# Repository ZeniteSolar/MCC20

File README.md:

# MCC20
**M**ódulo **C**ontrolador de **C**arga 2020  
Embarcação Guarapuvu II  
Equipe Zênite Solar  

### Sobre

Este módulo é responsável por gerenciar o carregamento da bateria e a operação do painel no seu ponto de maxima potencia 

#### Requisitos e Abordagens
1. [Encontrar o ponto de maxima potencia (MPP) do painel solar](#codigo)
    - Utilizar a tecnica perturbar e observar (p&o) para achar o MPP
    - Ao iniciar varrer o duty cicle para iniciar no MPP
    - Se a potencia for 0 fazer o barrido novamente 
2. Medir a Potencia do painel
    - Usar um ina826 para medir a tensao do painel
    - Usar um ina240 para medir a corrente do painel
    
3. Eficiencia energetica
    - Indutores
        - Utilizar fios em paralelo para diminuir o *skin effect*
        - Utilizar indutor acoplado (não implementado)
    - Capacitores
        - Utilizar capacitores SMD com baixa ESR
    - Chaves
        - Utilizar snubber para amortecer oscilações e picos de tensão
        - Utilizar chaves com baixa Rdson e rapidas
        - Utilizar conversor sincrono (não implementado)
    - Frequencia
        - Utilizar frequencia que tenha uma boa relação entre perdas nas chaves e volume do conversor
    - Layout
        - Baixa indutancia no braço (entre chaves)
        - Trilhas curtas
    - Snubber
        - Equilibrio entre sobre-tensão nas chaves e potencia dissipada
4. Robustez
    - Chaves em regime seguro
        - Snubber
        - Layout
    - Proteção *under load* (nao implementado)
    - Capacitores em regime seguro
        - Tensao maxima >Vpan+Vbat
    - Tolerancia termica
        - Projetar assumindo que a temperatura ambiente é 50°
    - Layout simples de montar por metodo artesanal (transferencia termica)

```
testee
```

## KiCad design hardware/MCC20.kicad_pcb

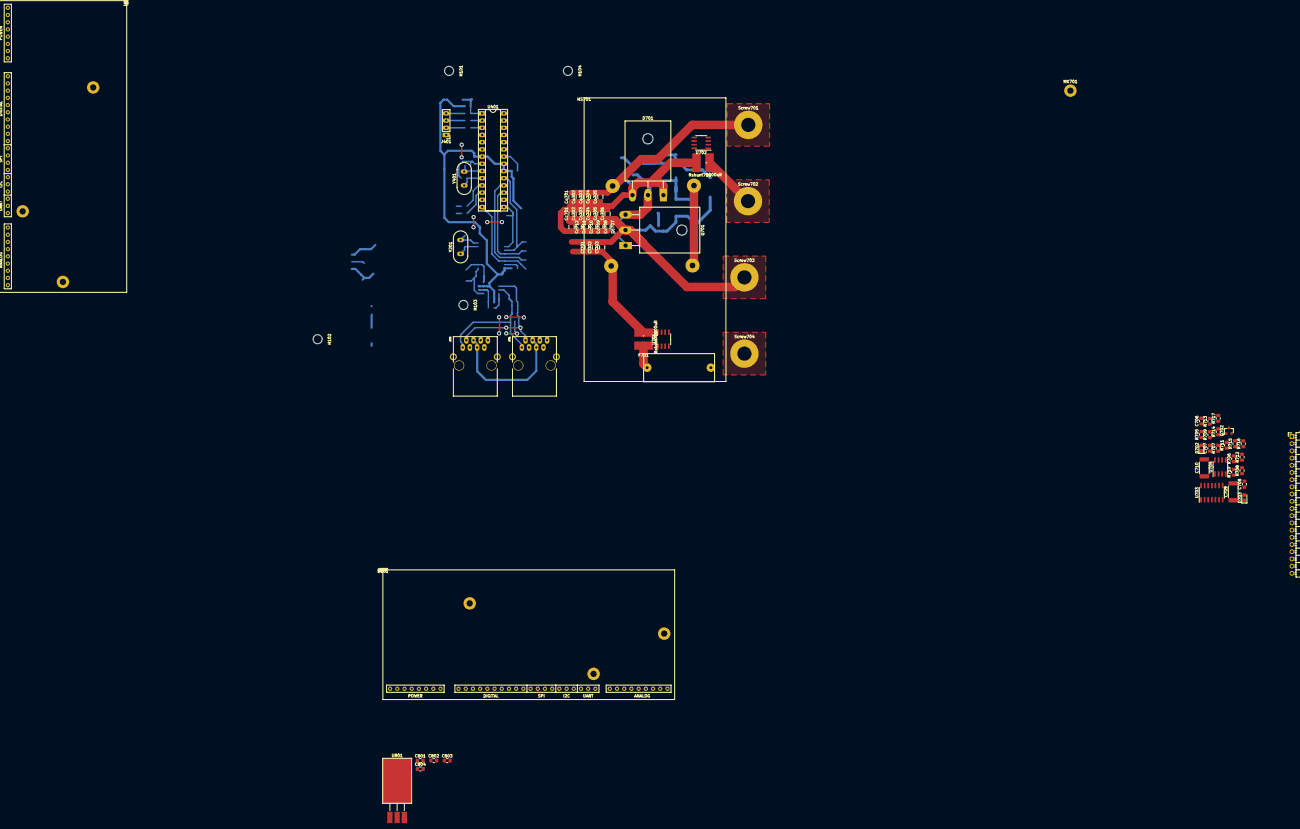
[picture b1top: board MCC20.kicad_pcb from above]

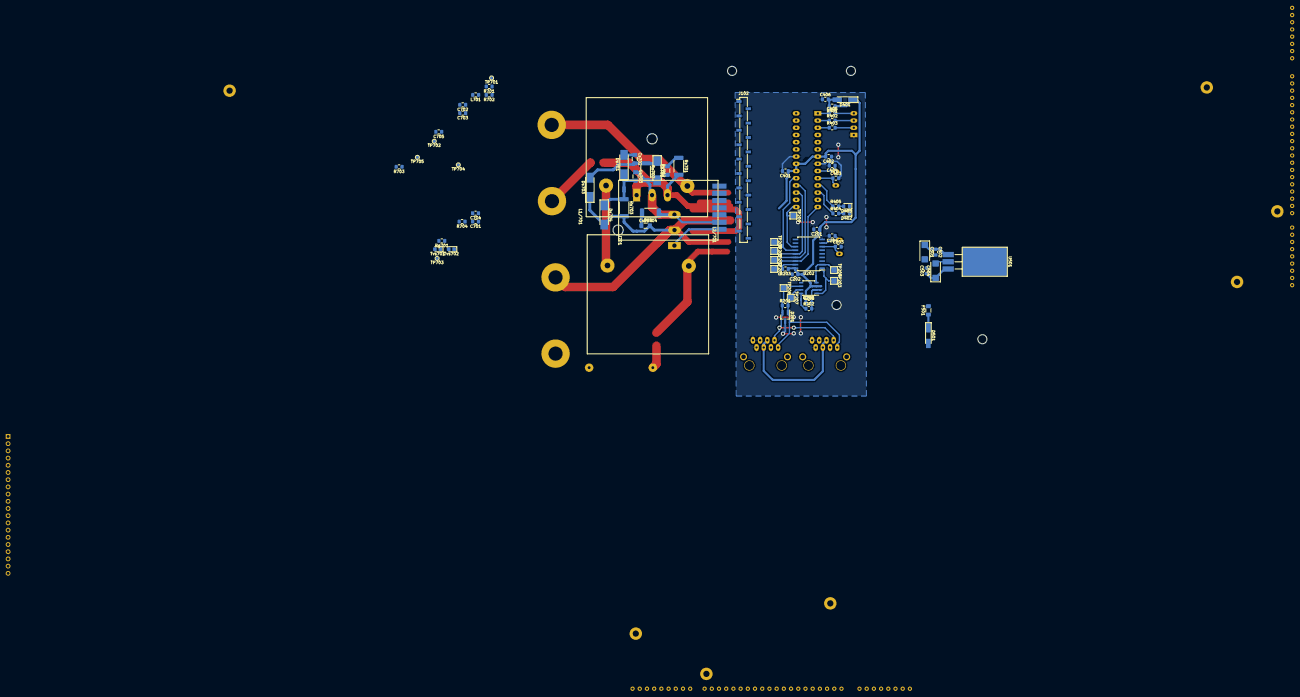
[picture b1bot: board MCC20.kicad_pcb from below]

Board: 2 copper layers, 149 parts (75 on the bottom side), 79 nets.

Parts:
C201, C202, C205, C401, C402, C405, C406, C502, C503, C701, C702, C703, C704, C708, C802, C803: 100nF; C_0805_2012Metric_Pad1.15x1.40mm_HandSolder
C203, C204, C403, C404: 22pF; C_0805_2012Metric_Pad1.15x1.40mm_HandSolder
C501, C504: 1uF; CP_EIA-6032-20_AVX-F_Pad2.25x2.35mm_HandSolder
C705, C801, C804: 10uF; C_0805_2012Metric_Pad1.15x1.40mm_HandSolder
C706: 100n; C_0805_2012Metric_Pad1.15x1.40mm_HandSolder
C707: 1n; C_0805_2012Metric_Pad1.15x1.40mm_HandSolder
C709, C710: 10u; C_2512_6332Metric_Pad1.52x3.35mm_HandSolder
Cc701, Cc702, Cc703, Cc704, Cc705, Cc706, Cc707, Cc708, Cc709, Cc710, Cc711, Cc712: 1uF 100V; C_1206_3216Metric_Pad1.42x1.75mm_HandSolder
Ci701, Ci702, Ci703: 4,7uF 50V; C_1206_3216Metric_Pad1.42x1.75mm_HandSolder
Co701, Co702, Co703, Co704, Co705: 2.2uF 100V; C_1206_3216Metric_Pad1.42x1.75mm_HandSolder
Cs701, Cs702, Cs703, Cs704: 100nF; C_1206_3216Metric_Pad1.42x1.75mm_HandSolder
D201: pesd1can; SOT-23_Handsoldering
D401, D501: LL4148; D_MiniMELF_Handsoldering
D402, D403: LED_RED; LED_0805_2012Metric_Pad1.15x1.40mm_HandSolder
D701: 80CPQ150PbF; TO-247-3_Horizontal_TabUp
D702, D703: D_TVS; D_0805_2012Metric_Castellated
Ds701, Ds702, Ds703, Ds704: BYD77; D_MELF_Handsoldering
F501: 500mA; Fuse_1206_3216Metric_Pad1.42x1.75mm_HandSolder
F701: Fuse; Porta_Fusivel
H101, H102, H103, H104: MountingHole; MountingHole_3.2mm_M3
HS701: Heatsink; hs10425
J101: Conn_01x20; PinHeader_1x20_P2.54mm_Horizontal
J102: Conn_01x20; PinSocket_1x20_P2.54mm_Vertical_SMD_Pin1Left
J401: USART; PinHeader_1x04_P2.54mm_Vertical
J601, J602: RJ45; RJ45_YH59_01
J701: Driver_INEP; Driver_(INEP)_SMD
L1/701, L2/701: L_Core_Iron_Small; Inductor_Nocoupled
L701: L_Small; L_0805_2012Metric_Pad1.15x1.40mm_HandSolder
MK701: Mounting_Hole; MountingHole_2.2mm_M2_Pad
Q701: IRFP4321PbF; TO-247-3_Horizontal_TabUp
Q702: Q_NPN_Darlington_BEC; SOT-23
R201: 120; R_0805_2012Metric_Pad1.15x1.40mm_HandSolder
R202: 4k7; R_0805_2012Metric_Pad1.15x1.40mm_HandSolder
R203, R401, R705, R706, R707: 10k; R_0805_2012Metric_Pad1.15x1.40mm_HandSolder
R402, R403, R404, R405: 1k; R_0805_2012Metric_Pad1.15x1.40mm_HandSolder
R701, R702: 330k; R_0805_2012Metric_Pad1.15x1.40mm_HandSolder
R703: 560k; R_0805_2012Metric_Pad1.15x1.40mm_HandSolder
R704: 39k; R_0805_2012Metric_Pad1.15x1.40mm_HandSolder
R708: 8.2k; R_0805_2012Metric_Pad1.15x1.40mm_HandSolder
R709: 75k; R_0805_2012Metric_Pad1.15x1.40mm_HandSolder
R710: 15k; R_0805_2012Metric_Pad1.15x1.40mm_HandSolder
R711: 12k; R_0805_2012Metric_Pad1.15x1.40mm_HandSolder
R712, R713: 150; R_0805_2012Metric_Pad1.15x1.40mm_HandSolder
R714: 100k; R_0805_2012Metric_Pad1.15x1.40mm_HandSolder
R715: 56k; R_0805_2012Metric_Pad1.15x1.40mm_HandSolder
R716: 220; R_0805_2012Metric_Pad1.15x1.40mm_HandSolder
R717: 100; R_0805_2012Metric_Pad1.15x1.40mm_HandSolder
Rg701: 10k; R_0805_2012Metric_Pad1.15x1.40mm_HandSolder
Rs701, Rs702, Rs703, Rs704: 100; R_2512_6332Metric_Pad1.52x3.35mm_HandSolder
Rshunt701, Rshunt702: 1500uR; PML100HZPJV0L5
Screw701: +B; MountingHole_5mm_Pad
Screw702: -B; MountingHole_5mm_Pad
Screw703: +P; MountingHole_5mm_Pad
Screw704: -P; MountingHole_5mm_Pad
TP201: SI; TestPoint_Pad_2.0x2.0mm
TP202: SO; TestPoint_Pad_2.0x2.0mm
TP203: TXCAN; TestPoint_Pad_2.0x2.0mm
TP204: RXCAN; TestPoint_Pad_2.0x2.0mm
TP205: SC; TestPoint_Pad_2.0x2.0mm
TP206: SCK; TestPoint_Pad_2.0x2.0mm
TP207: CAN_H; TestPoint_Pad_2.0x2.0mm
TP208: CAN_L; TestPoint_Pad_2.0x2.0mm
TP209: INT; TestPoint_Pad_2.0x2.0mm
TP701, TP702, TP703, TP704, TP705: TestPoint_Probe; TestPoint_Pad_D1.0mm
Tvs701, Tvs702: Tvs; D_0805_2012Metric_Castellated
U101, U102: ZCS; ZCS18
U201: MCP2551-I/SN; SOIC-8_3.9x4.9mm_P1.27mm
U202: MCP2515-xSO; SOIC-18W_7.5x11.6mm_P1.27mm
U401: ATMEGA328P-PU; DIP-28_W7.62mm_Socket
U501: LM7805; TO-220-3_Horizontal_TabDown_SMD
U701, U702: INA240A4D; SOIC-8_3.9x4.9mm_P1.27mm
U703: LM324; SOIC-14_3.9x8.7mm_P1.27mm
U704: INA826; SOIC-8_3.9x4.9mm_P1.27mm
U801: LM7812_TO220; TO-220-3_Horizontal_TabDown_SMD
Y201, Y401: 16MHz; Crystal_HC49-U_Vertical

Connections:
+5V: C201.1, C202.1, C205.1, C401.1, C402.2, C503.1, C504.1, C701.2, C702.2, D401.1, J102.20, R203.1, R401.1, Tvs701.1, Tvs702.1, U102.5, U201.3, U202.18, U401.7, U401.20, U401.21, U501.3, U701.6, U702.6
+5VA: C706.2, C708.1, J101.20, R705.2, R714.2, U703.4, U704.8
+12V: C703.1, C803.1, C804.1, L701.1, U801.3
/BatOVInterrupt: J102.17, U101.9
/CANBUS CONN/CAN_H: D201.1, J601.1, J602.1, R201.2, TP207.1, U201.7
/CANBUS CONN/CAN_L: D201.2, J601.2, J602.2, R201.1, TP208.1, U201.6
/CANBUS/CS: TP205.1, U202.16, U401.14
/CANBUS/INT: TP209.1, U202.12, U401.15
/CANBUS/RXCAN: TP204.1, U201.4, U202.2
/CANBUS/TXCAN: TP203.1, U201.1, U202.1
/MCU/LED1: R405.1, U401.11
/MCU/LED2: R404.1, U401.12
/MCU/PWM: U102.15, U401.16
/MCU/RESET: C405.1, C406.2, D401.2, R401.2, U401.1
/MCU/USART_RX: R402.1, U401.2
/MCU/USART_TX: R403.1, U401.3
/MCU/V_Ibat_ADC: U102.32, U401.26
/MCU/V_Ipanel_ADC: U102.31, U401.24
/MCU/V_Vbat_ADC: U102.34, U401.25
/MCU/V_Vpanel_ADC: U102.33, U401.23
/MISO: TP202.1, U202.15, U401.18
/MOSI: TP201.1, U202.14, U401.17
/POWER SUPPLY/+18V_IN: D501.2, J601.4, J601.5, J602.4, J602.5
/PWM: J102.18, J701.6, U101.15
/SCK: TP206.1, U202.13, U401.19
/Sheet5F261196/+B: Co701.2, Co702.2, Co703.2, Co704.2, Co705.2, L1/701.2, R703.1, Screw701.1
/Sheet5F261196/+Vp: Cc701.1, Cc702.1, Cc703.1, Cc704.1, Cc705.1, Cc706.1, Cc707.1, Cc708.1, Cc709.1, Cc710.1, Cc711.1, Cc712.1, Ci701.2, Ci702.2, Ci703.2, Cs704.2, Ds703.1, Ds704.2, Q701.2, R701.1, R702.2, Rs703.2, Screw703.1, TP703.1
/Sheet5F261196/-B: Cc701.2, Cc702.2, Cc703.2, Cc704.2, Cc705.2, Cc706.2, Cc707.2, Cc708.2, Cc709.2, Cc710.2, Cc711.2, Cc712.2, Co701.1, Co702.1, Co703.1, Co704.1, Co705.1, Cs702.1, D701.1, D701.3, Ds701.2, Rs701.2, Rshunt701.2, TP702.1, U702.1
/Sheet5F261196/-P_unfused: F701.2, Screw704.1
/Sheet5F261196/-Vp: Ci701.1, Ci702.1, Ci703.1, L2/701.1, Rshunt702.1, U701.8
/Sheet5F261196/BatShunt+: Rshunt701.1, Screw702.1, U702.8
/Sheet5F261196/HG: J701.1, Q701.1, Rg701.1, TP705.1
/Sheet5F261196/HS: Cs701.1, Cs703.1, D701.2, Ds702.2, J701.2, L1/701.1, L2/701.2, Q701.3, Rg701.2, Rs702.2, Rs704.1, TP701.1, TP704.1
/Sheet5F261196/PanelShunt-: F701.1, Rshunt702.2, U701.1
/Sheet5F261196/V_Ibat: U101.32, U702.5
/Sheet5F261196/V_Ipanel: U101.31, U701.5
/Sheet5F261196/V_Vbat: J102.12, R703.2, R704.2
/Sheet5F261196/V_Vpanel+: J102.1, R702.1
/Sheet5F261196/V_Vpanel-: J102.2, R701.2
/Sheet5F261196/Vcc: C704.1, C705.1, J701.5, L701.2
/Signal/BatOVInterrupt: J101.17, R716.2, U703.1
/Signal/PWM: J101.18, R717.1
/Signal/V_Vbat: C707.1, J101.12, U703.10, U703.13
/Signal/V_Vbat_ADC: C709.1, D703.1, J101.15, R712.2
/Signal/V_Vpanel+: J101.1, R707.2, R708.1, U704.1
/Signal/V_Vpanel-: J101.2, R706.1, R708.2, U704.4
/Signal/V_Vpanel_ADC: C710.1, D702.1, J101.4, R713.1
GND: C201.2, C202.2, C203.2, C204.2, C205.2, C401.2, C402.1, C403.2, C404.2, C406.1, C501.2, C502.2, C503.2, C504.2, C701.1, C702.1, C703.2, C704.2, C705.2, C801.2, C802.2, C803.2, C804.2, D201.3, D402.1, D403.1, J102.3, J102.13, J102.14, J102.19, J401.1, J601.3, J601.6, J601.7, J601.8, J602.3, J602.6, J602.7, J602.8, J701.7, R202.2, R704.1, Tvs701.2, Tvs702.2, U101.2, U101.3, U101.4, U101.6, U101.7, U101.8, U101.18, U101.22, U101.25, U101.28, U101.37, U102.2, U102.3, U102.4, U102.6, U102.7, U102.8, U102.18, U102.22, U102.25, U102.28, U102.37, U201.2, U202.9, U401.8, U401.22, U501.2, U701.2, U701.3, U701.4, U701.7, U702.2, U702.3, U702.4, U702.7, U801.2
GNDA: C706.1, C707.2, C708.2, C709.2, C710.2, D702.2, D703.2, J101.3, J101.13, J101.14, J101.19, Q702.2, R706.2, R707.1, R709.1, R715.1, U703.5, U703.11, U704.5, U704.6
unnamed: C203.1, U202.7, Y201.1
unnamed: C204.1, U202.8, Y201.2
unnamed: C403.1, U401.10, Y401.1
unnamed: C404.1, U401.9, Y401.2
unnamed: C405.2, J401.4
unnamed: Cs701.2, Rs701.1
unnamed: Cs702.2, Ds702.1, Ds703.2, Rs702.1
unnamed: Cs703.2, Ds701.1, Ds704.1, Rs703.1
unnamed: Cs704.1, Rs704.2
unnamed: D402.2, R404.2
unnamed: D403.2, R405.2
unnamed: D501.1, F501.1
unnamed: J102.4, U101.33
unnamed: J102.15, U101.34
unnamed: J401.2, R403.2
unnamed: J401.3, R402.2
unnamed: Q702.1, R716.1
unnamed: Q702.3, R717.2
unnamed: R202.1, U201.8
unnamed: R203.2, U202.17
unnamed: R705.1, R709.2, R711.2, U703.12
unnamed: R710.1, U704.3
unnamed: R710.2, U704.2
unnamed: R711.1, U703.2, U703.14
unnamed: R712.1, U703.8, U703.9
unnamed: R713.2, U704.7
unnamed: R714.1, R715.2, U703.3
unnamed: U703.6, U703.7
VCC: C501.1, C502.1, F501.2, U102.1, U501.1
VCCQ: C801.1, C802.1, U101.1, U801.1

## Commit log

2020-04-25 inicio
2020-04-25 compiling
2020-04-25 fake_painel_model
2020-04-25 falha quando corrente é 0
2020-04-27 Simple simulator using bisect to solve the circuit.
2020-04-29 soft task
2020-04-29 mppt ok
2020-04-29 pouca coisa
2020-04-30 Fixing run script.
2020-04-30 Some simple comments
2020-04-30 Bisect solver moved to solvers.[hc]
2020-04-30 panel_model moved to panel_model.[hc]
2020-04-30 removed .ropeproject
2020-04-30 create_fake_painel.py is not necessary
2020-04-30 Asynchronous unix domain stream socket server implemented
2020-05-01 Client abruptly disconnection solved.
2020-05-01 Run could clean remaining sockets
2020-05-01 Working socket
2020-05-01 Initial implementation: plotting only one data
2020-05-01 realtime-plot done
2020-05-01 verbose option added
2020-05-02 params vector is an argument for panel_model function
2020-05-02 fixing vector pointers
2020-05-02 Added flags to a better code quality
2020-05-02 warnings fixed
2020-05-02 no more warnings
2020-05-02 Blank project
2020-05-29 Makefile added
2020-05-29 fixing variable declaration
2020-05-29 cleaning
2020-05-30 enabling flags in makefile
2020-05-30 Regula Falsi implemented, but not tested
2020-05-30 enabling regula falsi
2020-08-01 imported MVC hardware
2020-08-01 cuk imported and cleared
2020-08-02 Signal and Cuk imported
2020-08-02 trash
2020-08-02 schematic and footprint
2020-08-02 sch DRC and THT components position
2020-08-03 parte de potencia
2020-08-03 initial
2020-08-03 snubber

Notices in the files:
parts and their libraries:
Copyright 2016 Accelerated Designs. All rights reserved.
